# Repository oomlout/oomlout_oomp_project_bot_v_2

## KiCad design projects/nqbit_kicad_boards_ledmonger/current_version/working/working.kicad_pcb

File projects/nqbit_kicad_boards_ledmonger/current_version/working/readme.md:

# kicad_boards
 
## summary 
* id: nqbit_kicad_boards_ledmonger
* user: nqbit
* name: kicad_boards
* board: ledmonger
* repo: https://github.com/nqbit/kicad-boards
* src_file_repo_kicad_pcb: ledmonger/ledmonger.kicad_pcb
* src_file_repo_kicad_pcb_link: https://github.com/nqbit/kicad-boards/tree/master/ledmonger/ledmonger.kicad_pcb

* src_file_repo_sch: ledmonger/ledmonger.sch
* src_file_repo_sch_link: https://github.com/nqbit/kicad-boards/tree/master/ledmonger/ledmonger.sch
* full details link: https://github.com/oomlout/oomlout_oomp_project_bot_v_2/tree/main/projects/nqbit_kicad_boards_ledmonger/current_version/working

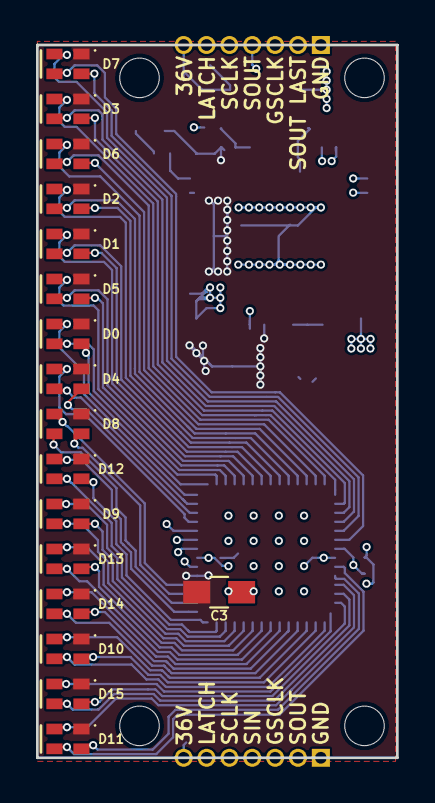
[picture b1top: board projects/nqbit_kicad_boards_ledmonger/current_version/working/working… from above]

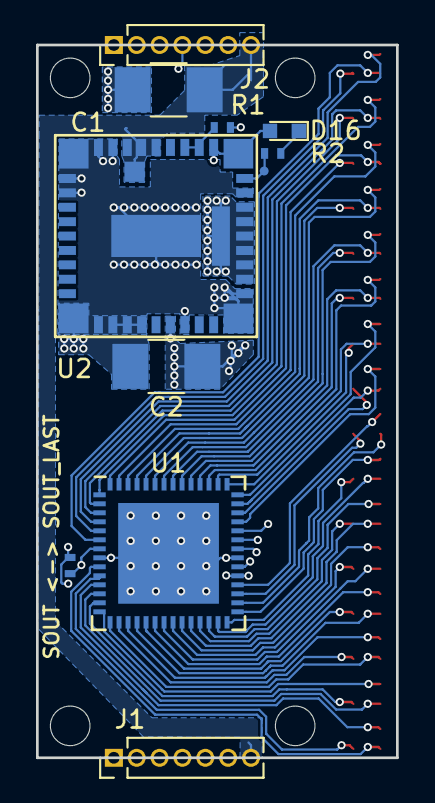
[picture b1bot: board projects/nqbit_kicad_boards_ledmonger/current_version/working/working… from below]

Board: 4 copper layers, 20.0 x 39.6 mm, 28 parts (11 on the bottom side), 60 nets.

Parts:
C1, C2: 100uF; C_1210_HandSoldering
C3: 100nF; C_0805_HandSoldering
D0, D1, D2, D3, D4, D5, D6, D7, D8, D9, D10, D11, D12, D13, D14, D15: LED_ARGB; LED_HSMF-C114
D16: LED_Small; LED_0603
J1, J2: Conn_01x07; Pin_Header_Straight_1x07_Pitch1.27mm
JP1: Jumper_NC_Small; R_0402_NoSilk
R1, R2: 8.06k; R_0402_NoSilk
TP0: PWRGD; TEST_POINT_0.5mm
U1: TLC5955; QFN-56-1EP_7x7mm_Pitch0.5mm
U2: LMZ34202; 43-BQFN-10mmx10mm

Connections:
+3V3: C2.1, C3.1, D0.1, D1.1, D2.1, D3.1, D4.1, D5.1, D6.1, D7.1, D8.1, D9.1, D10.1, D11.1, D12.1, D13.1, D14.1, D15.1, D16.2, U1.33, U2.7, U2.13, U2.14, U2.15, U2.16, U2.17, U2.18, U2.21, U2.22, U2.43
/GSCLK: J1.3, J2.3, U1.34
/LAT: J1.6, J2.6, U1.38
/LEDB0: D0.4, U1.42
/LEDB1: D1.4, U1.48
/LEDB2: D2.4, U1.51
/LEDB3: D3.4, U1.1
/LEDB4: D4.4, U1.39
/LEDB5: D5.4, U1.45
/LEDB6: D6.4, U1.54
/LEDB7: D7.4, U1.4
/LEDB8: D8.4, U1.32
/LEDB9: D9.4, U1.26
/LEDB10: D10.4, U1.17
/LEDB11: D11.4, U1.11
/LEDB12: D12.4, U1.29
/LEDB13: D13.4, U1.23
/LEDB14: D14.4, U1.20
/LEDB15: D15.4, U1.14
/LEDG0: D0.3, U1.44
/LEDG1: D1.3, U1.50
/LEDG2: D2.3, U1.53
/LEDG3: D3.3, U1.3
/LEDG4: D4.3, U1.41
/LEDG5: D5.3, U1.47
/LEDG6: D6.3, U1.56
/LEDG7: D7.3, U1.6
/LEDG8: D8.3, U1.30
/LEDG9: D9.3, U1.24
/LEDG10: D10.3, U1.15
/LEDG11: D11.3, U1.9
/LEDG12: D12.3, U1.27
/LEDG13: D13.3, U1.21
/LEDG14: D14.3, U1.18
/LEDG15: D15.3, U1.12
/LEDR0: D0.2, U1.43
/LEDR1: D1.2, U1.49
/LEDR2: D2.2, U1.52
/LEDR3: D3.2, U1.2
/LEDR4: D4.2, U1.40
/LEDR5: D5.2, U1.46
/LEDR6: D6.2, U1.55
/LEDR7: D7.2, U1.5
/LEDR8: D8.2, U1.31
/LEDR9: D9.2, U1.25
/LEDR10: D10.2, U1.16
/LEDR11: D11.2, U1.10
/LEDR12: D12.2, U1.28
/LEDR13: D13.2, U1.22
/LEDR14: D14.2, U1.19
/LEDR15: D15.2, U1.13
/PWRGD: R2.2, TP0.1, U2.20
/SCLK: J1.5, J2.5, U1.37
/SIN: J1.4, U1.36
/SOUT: J2.4, JP1.1, U1.7
/SOUT_LAST: J1.2, J2.2, JP1.2
/V36P0: C1.1, J1.7, J2.7, U2.26, U2.27, U2.28, U2.42
/VADJ: R1.2, U2.23, U2.24
GND: C1.2, C2.2, C3.2, J1.1, J2.1, R1.1, U1.8, U1.35, U1.57, U2.1, U2.2, U2.3, U2.4, U2.5, U2.8, U2.11, U2.12, U2.19, U2.29, U2.30, U2.31, U2.32, U2.33, U2.41
unnamed: D16.1, R2.1

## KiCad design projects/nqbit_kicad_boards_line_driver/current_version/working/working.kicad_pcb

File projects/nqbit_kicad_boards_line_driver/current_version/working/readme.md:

# kicad_boards
 
## summary 
* id: nqbit_kicad_boards_line_driver
* user: nqbit
* name: kicad_boards
* board: line_driver
* repo: https://github.com/nqbit/kicad-boards
* src_file_repo_kicad_pcb: line_driver/line_driver.kicad_pcb
* src_file_repo_kicad_pcb_link: https://github.com/nqbit/kicad-boards/tree/master/line_driver/line_driver.kicad_pcb

* src_file_repo_sch: line_driver/line_driver.sch
* src_file_repo_sch_link: https://github.com/nqbit/kicad-boards/tree/master/line_driver/line_driver.sch
* full details link: https://github.com/oomlout/oomlout_oomp_project_bot_v_2/tree/main/projects/nqbit_kicad_boards_line_driver/current_version/working

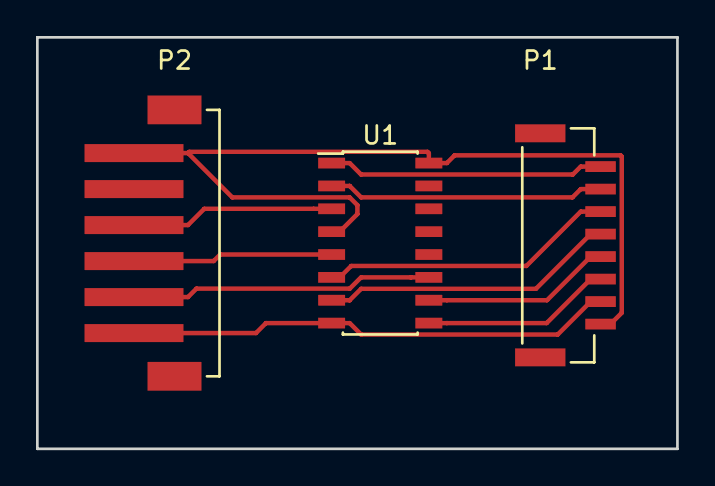
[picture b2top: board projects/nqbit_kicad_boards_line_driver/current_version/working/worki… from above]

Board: 2 copper layers, 35.6 x 22.9 mm, 3 parts (0 on the bottom side), 11 nets.

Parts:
P1: CONN_01X08; GH_1x8_TOP
P2: CONN_01X06; CONN_PH_1x6_TOP_SMT
U1: AM26LS32ACDR; SOIC-16_3.9x9.9mm_Pitch1.27mm

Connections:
GND: P1.2, P2.6, U1.8
unnamed: P1.3, U1.9
unnamed: P1.4, U1.10
unnamed: P1.5, U1.7
unnamed: P1.6, U1.6
unnamed: P1.7, U1.2
unnamed: P1.8, U1.1
unnamed: P2.3, U1.3
unnamed: P2.4, U1.5
unnamed: P2.5, U1.11
VCC: P1.1, P2.1, U1.4, U1.16

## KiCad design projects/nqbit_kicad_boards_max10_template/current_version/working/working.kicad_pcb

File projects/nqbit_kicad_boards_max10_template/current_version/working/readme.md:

# kicad_boards
 
## summary 
* id: nqbit_kicad_boards_max10_template
* user: nqbit
* name: kicad_boards
* board: max10_template
* repo: https://github.com/nqbit/kicad-boards
* src_file_repo_kicad_pcb: max10_template/max10_template.kicad_pcb
* src_file_repo_kicad_pcb_link: https://github.com/nqbit/kicad-boards/tree/master/max10_template/max10_template.kicad_pcb

* src_file_repo_sch: max10_template/max10_template.sch
* src_file_repo_sch_link: https://github.com/nqbit/kicad-boards/tree/master/max10_template/max10_template.sch
* full details link: https://github.com/oomlout/oomlout_oomp_project_bot_v_2/tree/main/projects/nqbit_kicad_boards_max10_template/current_version/working

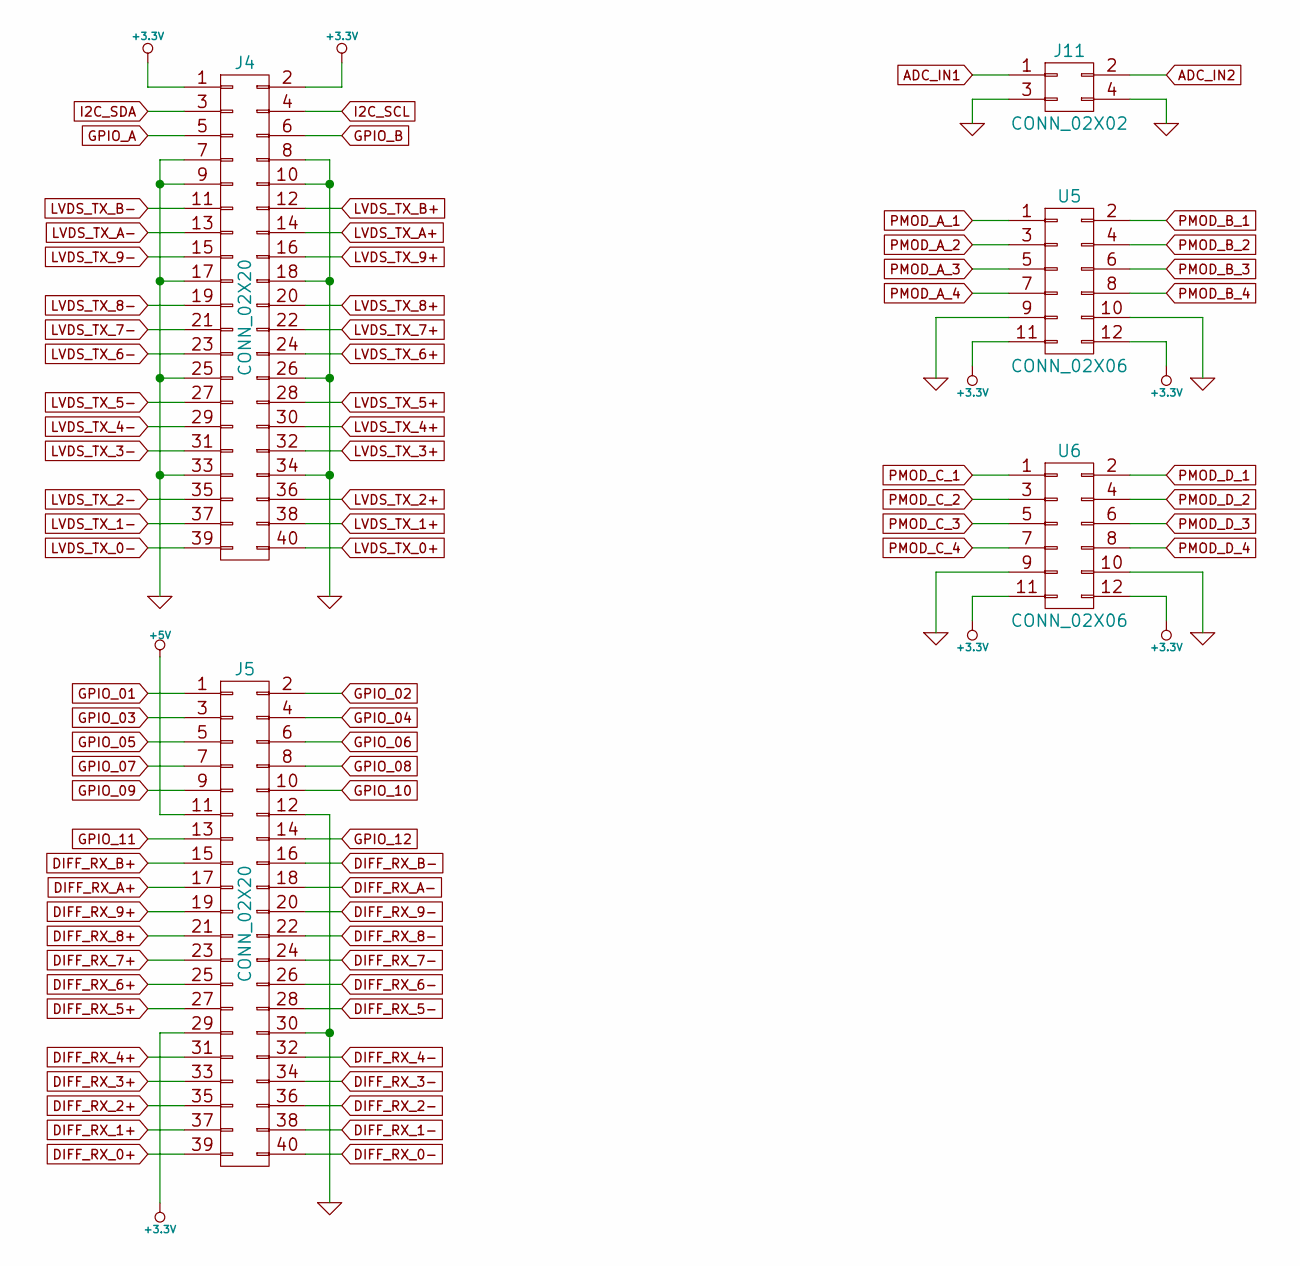
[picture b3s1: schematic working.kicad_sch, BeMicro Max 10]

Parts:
J4, J5: CONN_02X20; Pin_Header_Straight_2x20
J11: CONN_02X02; Pin_Header_Straight_2x02
U5, U6: CONN_02X06; Pin_Header_Straight_2x06

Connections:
+3.3V: J4.1, J4.2, J5.29, U5.11, U5.12, U6.11, U6.12
+5V: J5.11
ADC_IN1: J11.1
ADC_IN2: J11.2
DIFF_RX_0+: J5.39
DIFF_RX_0-: J5.40
DIFF_RX_1+: J5.37
DIFF_RX_1-: J5.38
DIFF_RX_2+: J5.35
DIFF_RX_2-: J5.36
DIFF_RX_3+: J5.33
DIFF_RX_3-: J5.34
DIFF_RX_4+: J5.31
DIFF_RX_4-: J5.32
DIFF_RX_5+: J5.27
DIFF_RX_5-: J5.28
DIFF_RX_6+: J5.25
DIFF_RX_6-: J5.26
DIFF_RX_7+: J5.23
DIFF_RX_7-: J5.24
DIFF_RX_8+: J5.21
DIFF_RX_8-: J5.22
DIFF_RX_9+: J5.19
DIFF_RX_9-: J5.20
DIFF_RX_A+: J5.17
DIFF_RX_A-: J5.18
DIFF_RX_B+: J5.15
DIFF_RX_B-: J5.16
GND: J4.7, J4.8, J4.9, J4.10, J4.17, J4.18, J4.25, J4.26, J4.33, J4.34, J5.12, J5.30, J11.3, J11.4, U5.9, U5.10, U6.9, U6.10
GPIO_01: J5.1
GPIO_02: J5.2
GPIO_03: J5.3
GPIO_04: J5.4
GPIO_05: J5.5
GPIO_06: J5.6
GPIO_07: J5.7
GPIO_08: J5.8
GPIO_09: J5.9
GPIO_10: J5.10
GPIO_11: J5.13
GPIO_12: J5.14
GPIO_A: J4.5
GPIO_B: J4.6
I2C_SCL: J4.4
I2C_SDA: J4.3
LVDS_TX_0+: J4.40
LVDS_TX_0-: J4.39
LVDS_TX_1+: J4.38
LVDS_TX_1-: J4.37
LVDS_TX_2+: J4.36
LVDS_TX_2-: J4.35
LVDS_TX_3+: J4.32
LVDS_TX_3-: J4.31
LVDS_TX_4+: J4.30
LVDS_TX_4-: J4.29
LVDS_TX_5+: J4.28
LVDS_TX_5-: J4.27
LVDS_TX_6+: J4.24
LVDS_TX_6-: J4.23
LVDS_TX_7+: J4.22
LVDS_TX_7-: J4.21
LVDS_TX_8+: J4.20
LVDS_TX_8-: J4.19
LVDS_TX_9+: J4.16
LVDS_TX_9-: J4.15
LVDS_TX_A+: J4.14
LVDS_TX_A-: J4.13
LVDS_TX_B+: J4.12
LVDS_TX_B-: J4.11
PMOD_A_1: U5.1
PMOD_A_2: U5.3
PMOD_A_3: U5.5
PMOD_A_4: U5.7
PMOD_B_1: U5.2
PMOD_B_2: U5.4
PMOD_B_3: U5.6
PMOD_B_4: U5.8
PMOD_C_1: U6.1
PMOD_C_2: U6.3
PMOD_C_3: U6.5
PMOD_C_4: U6.7
PMOD_D_1: U6.2
PMOD_D_2: U6.4
PMOD_D_3: U6.6
PMOD_D_4: U6.8

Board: 2 copper layers, 5 parts (0 on the bottom side), 2 nets, no tracks yet.

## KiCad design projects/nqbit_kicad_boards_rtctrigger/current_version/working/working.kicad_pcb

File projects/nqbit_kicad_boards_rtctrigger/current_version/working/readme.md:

# kicad_boards
 
## summary 
* id: nqbit_kicad_boards_rtctrigger
* user: nqbit
* name: kicad_boards
* board: rtctrigger
* repo: https://github.com/nqbit/kicad-boards
* src_file_repo_kicad_pcb: rtctrigger/rtctrigger.kicad_pcb
* src_file_repo_kicad_pcb_link: https://github.com/nqbit/kicad-boards/tree/master/rtctrigger/rtctrigger.kicad_pcb

* src_file_repo_sch: rtctrigger/rtctrigger.sch
* src_file_repo_sch_link: https://github.com/nqbit/kicad-boards/tree/master/rtctrigger/rtctrigger.sch
* full details link: https://github.com/oomlout/oomlout_oomp_project_bot_v_2/tree/main/projects/nqbit_kicad_boards_rtctrigger/current_version/working

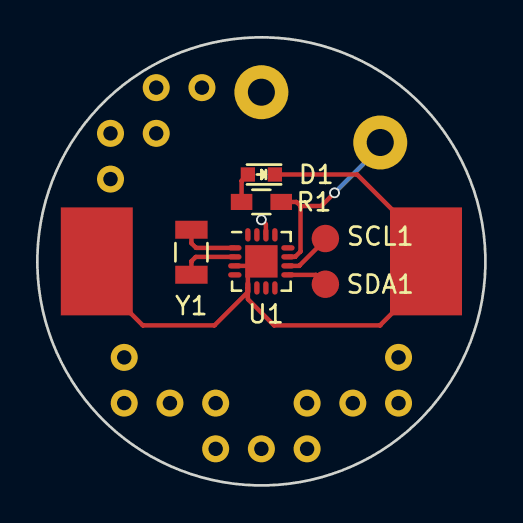
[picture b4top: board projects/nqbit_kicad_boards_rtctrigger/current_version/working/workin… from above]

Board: 2 copper layers, 24.9 x 24.9 mm, 11 parts (1 on the bottom side), 8 nets.

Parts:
BATT1: BATT; PAD_7MM
BATT2: BATT; Measurement_Point_Round-TH_Big
D1: LED; LED_0603
GND1, GND2: GND; RECT_6X4MM
OUT1: OUT; Measurement_Point_Round-TH_Big
R1: 300; R_0603_HandSoldering
SCL1: SCL; Measurement_Point_Round-SMD-Pad_Small
SDA1: SDA; Measurement_Point_Round-SMD-Pad_Small
U1: M41T62; QFN-16-1EP_3x3mm_Pitch0.5mm
Y1: Crystal_Small; FC-135

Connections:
+BATT: BATT1.1, BATT2.1, U1.14
GND: D1.1, GND1.1, GND2.1, U1.3, U1.5, U1.17
unnamed: D1.2, R1.2
unnamed: OUT1.1, R1.1, U1.11
unnamed: SCL1.1, U1.10
unnamed: SDA1.1, U1.9
unnamed: U1.1, Y1.2
unnamed: U1.2, Y1.1

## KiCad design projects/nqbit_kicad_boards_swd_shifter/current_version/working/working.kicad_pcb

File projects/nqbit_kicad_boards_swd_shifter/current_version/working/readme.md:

# kicad_boards
 
## summary 
* id: nqbit_kicad_boards_swd_shifter
* user: nqbit
* name: kicad_boards
* board: swd_shifter
* repo: https://github.com/nqbit/kicad-boards
* src_file_repo_kicad_pcb: swd_shifter/swd_shifter.kicad_pcb
* src_file_repo_kicad_pcb_link: https://github.com/nqbit/kicad-boards/tree/master/swd_shifter/swd_shifter.kicad_pcb

* src_file_repo_sch: swd_shifter/swd_shifter.sch
* src_file_repo_sch_link: https://github.com/nqbit/kicad-boards/tree/master/swd_shifter/swd_shifter.sch
* full details link: https://github.com/oomlout/oomlout_oomp_project_bot_v_2/tree/main/projects/nqbit_kicad_boards_swd_shifter/current_version/working

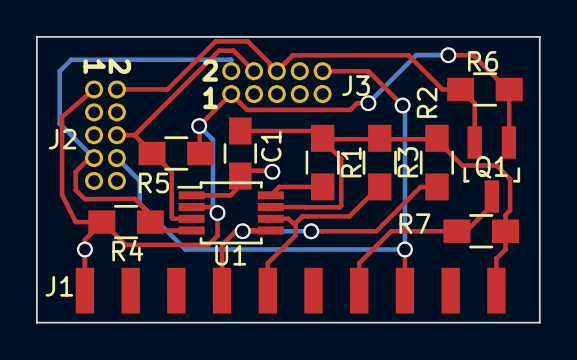
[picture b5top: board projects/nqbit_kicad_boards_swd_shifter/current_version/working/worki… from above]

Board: 2 copper layers, 27.9 x 15.9 mm, 13 parts (0 on the bottom side), 12 nets.

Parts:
C1: 0.1 uF; C_0805_HandSoldering
J1: JTAG_STLINKV2; EDGE_CONNECTOR_2x10_2.54MM
J2: PACKET_TRACE_PORT; HEADER_PTH_MALE_2x5_1.27MM
J3: JTAG_10_PIN; HEADER_PTH_MALE_2x5_1.27MM
Q1: BSS138; SOT-23_Handsoldering
R1: 200k; R_0805_HandSoldering
R2, R3, R4, R5: 1k; R_0805_HandSoldering
R6, R7: 10k; R_0805_HandSoldering
U1: PCA9306; MSOP-8_3x3mm_Pitch0.65mm

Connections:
3V3: C1.1, J1.19, R1.1, R2.1, R3.1, R7.1, U1.7
/EN: R1.2, U1.8
/NRST: J1.15, J2.8, J3.10
/ST_SCL: J1.9, R3.2, U1.6
/ST_SDA: J1.7, R2.2, U1.5
/T_SCL: J2.6, J3.4, R5.2, U1.3
/T_SDA: J2.7, J3.2, R4.2, U1.4
/VREF: J1.1, J1.2
GND: C1.2, J1.4, J1.6, J1.8, J1.10, J1.12, J1.14, J1.16, J1.18, J1.20, J2.5, J3.3, J3.5, J3.9, U1.1
ST_SWO: J1.13, Q1.3, R7.2
T_SWO: J2.2, J3.6, Q1.2, R6.2
VCC: J2.1, J3.1, Q1.1, R4.1, R5.1, R6.1, U1.2
